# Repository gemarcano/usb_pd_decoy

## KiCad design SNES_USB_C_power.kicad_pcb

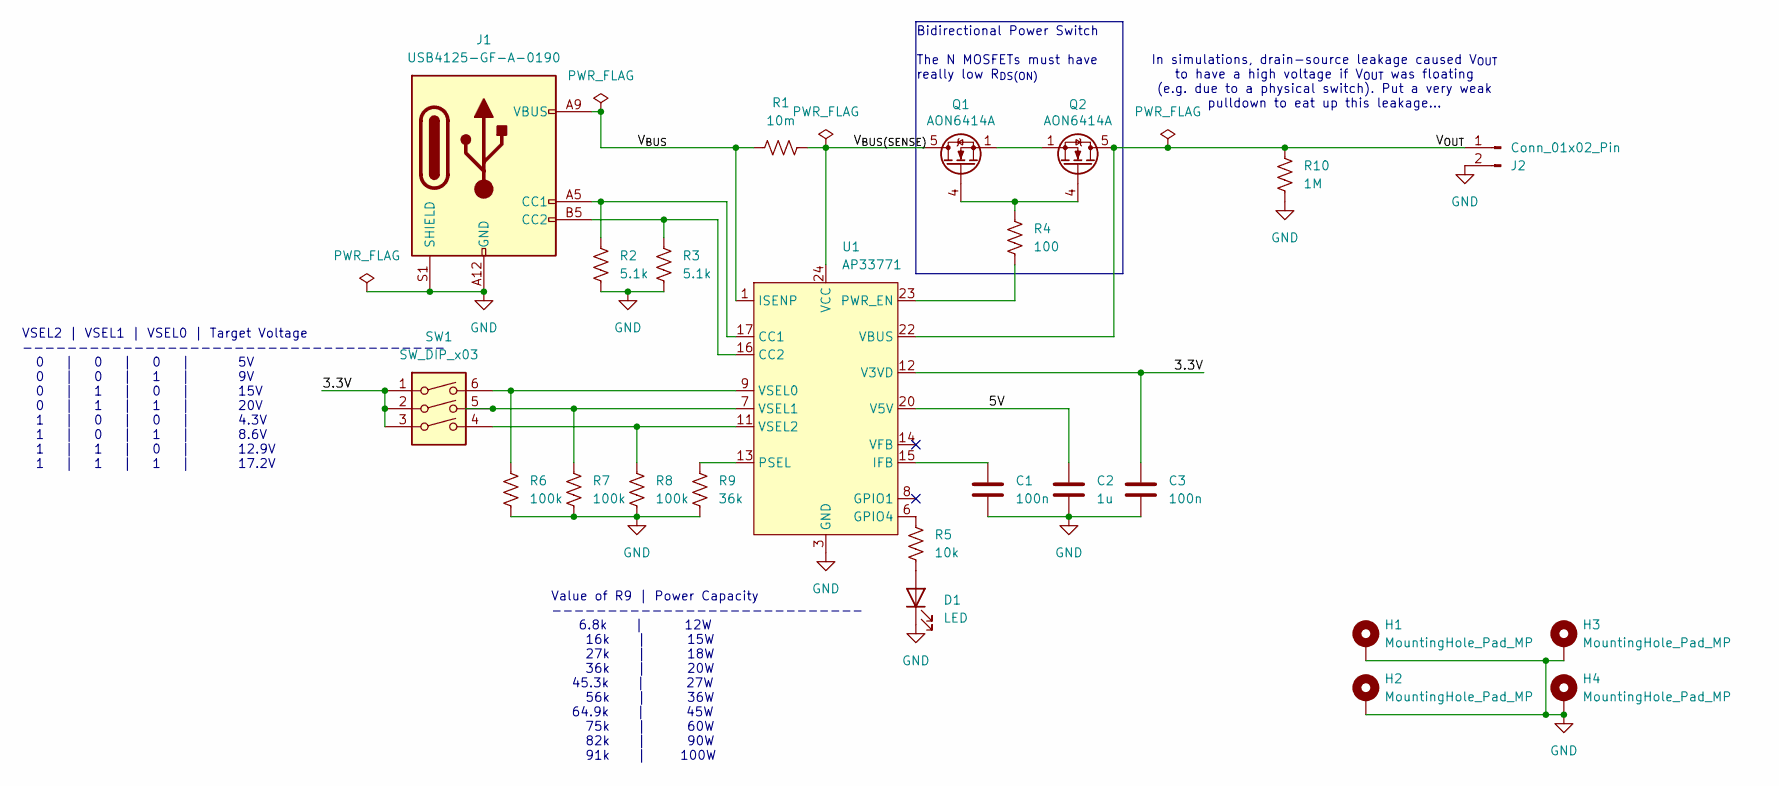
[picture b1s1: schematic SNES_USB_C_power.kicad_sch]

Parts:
C1, C3: 100n; C_0603_1608Metric_Pad1.08x0.95mm_HandSolder
C2: 1u; C_0603_1608Metric_Pad1.08x0.95mm_HandSolder
D1: LED; LED_0603_1608Metric
H1, H2, H3, H4: MountingHole_Pad_MP; MountingHole_3.2mm_M3_Pad_Via
J1: USB4125-GF-A-0190; USB_C_USB4125-GF-A_Hand_Solder
J2: Conn_01x02_Pin; PinHeader_1x02_P2.54mm_Vertical
Q1, Q2: AON6414A; AO_DFN-8-1EP_5.55x5.2mm_P1.27mm_EP4.12x4.6mm; Manufacturer Part Number AON6414A; Digikey Part Number 785-1226-1-ND
R1: 10m; R_0612_1632Metric_Pad1.18x3.40mm_HandSolder; Manufacturer Part Number PE0612FKF070R01L; Digikey Part Number YAG6109CT-ND
R2, R3: 5.1k; R_0603_1608Metric_Pad0.98x0.95mm_HandSolder
R4: 100; R_0603_1608Metric_Pad0.98x0.95mm_HandSolder
R5: 10k; R_0603_1608Metric_Pad0.98x0.95mm_HandSolder
R6, R7, R8: 100k; R_0603_1608Metric_Pad0.98x0.95mm_HandSolder
R9: 36k; R_0603_1608Metric_Pad0.98x0.95mm_HandSolder
R10: 1M; R_0603_1608Metric_Pad0.98x0.95mm_HandSolder
SW1: SW_DIP_x03; DIP-6_W7.62mm_LongPads; Manufacturer Part Number DS04-254-2L-03BK; Digikey Part Number 2223-DS04-254-2L-03BK-ND
U1: AP33771; QFN-24-1EP_4x4mm_P0.5mm_EP2.7x2.7mm; Manufacturer Part Number AP33771DKZ-13; Digikey Part Number 31-AP33771DKZ-13CT-ND

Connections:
/3.3V: C3.1, SW1.1, SW1.2, SW1.3, U1.12 (V3VD)
/5V: C2.1, U1.20 (V5V)
/V_{BUS(SENSE)}: Q1.5 (D), R1.2, U1.24 (VCC)
/V_{BUS}: J1.A9 (VBUS), J1.B9 (VBUS), R1.1, U1.1 (ISENP)
/V_{OUT}: J2.1, Q2.5 (D), R10.2, U1.22 (VBUS)
GND: C1.2, C2.2, C3.2, D1.1 (K), H1.1, H2.1, H3.1, H4.1, J1.A12 (GND), J1.B12 (GND), J1.S1 (SHIELD), J2.2, R2.1, R3.1, R6.1, R7.1, R8.1, R9.1, R10.1, U1.3 (GND), U1.25 (GND)
unnamed: D1.2 (A), R5.1
unnamed: J1.A5 (CC1), R2.2, U1.17 (CC1)
unnamed: J1.B5 (CC2), R3.2, U1.16 (CC2)
unnamed: Q1.4 (G), Q2.4 (G), R4.2
unnamed: Q1.1 (S), Q1.2 (S), Q1.3 (S), Q2.1 (S), Q2.2 (S), Q2.3 (S)
unnamed: R5.2, U1.6 (GPIO4)
unnamed: C1.1, U1.15 (IFB)
unnamed: R9.2, U1.13 (PSEL)
unnamed: R4.1, U1.23 (PWR_EN)
unnamed: R6.2, SW1.6, U1.9 (VSEL0)
unnamed: R7.2, SW1.5, U1.7 (VSEL1)
unnamed: R8.2, SW1.4, U1.11 (VSEL2)

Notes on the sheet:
In simulations, drain-source leakage caused V_{OUT} to have a high voltage if V_{OUT} was floating (e.g. due to a physical switch). Put a very weak pulldown to eat up this leakage...
Bidirectional Power Switch The N MOSFETs must have really low R_{DS(ON)}
VSEL2 | VSEL1 | VSEL0 | Target Voltage -------------------------------------- 0 | 0 | 0 | 5V 0 | 0 | 1 | 9V 0 | 1 | 0 | 15V 0 | 1 | 1 | 20V 1 | 0 | 0 | 4.3V 1 | 0 | 1 | 8.6V 1 | 1 | 0 | 12.9V 1 | 1 | 1 | 17.2V
Value of R9 | Power Capacity ---------------------------- 6.8k | 12W 16k | 15W 27k | 18W 36k | 20W 45.3k | 27W 56k | 36W 64.9k | 45W 75k | 60W 82k | 90W 91k | 100W

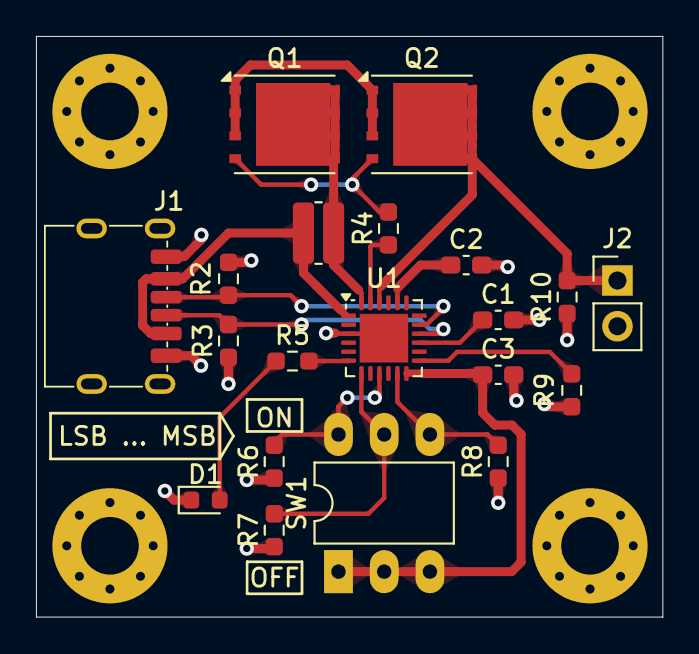
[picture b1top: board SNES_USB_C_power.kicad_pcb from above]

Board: 2 copper layers, 34.8 x 32.3 mm, 24 parts (0 on the bottom side), 18 nets.

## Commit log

2024-06-12 Update title and revision in schematic
